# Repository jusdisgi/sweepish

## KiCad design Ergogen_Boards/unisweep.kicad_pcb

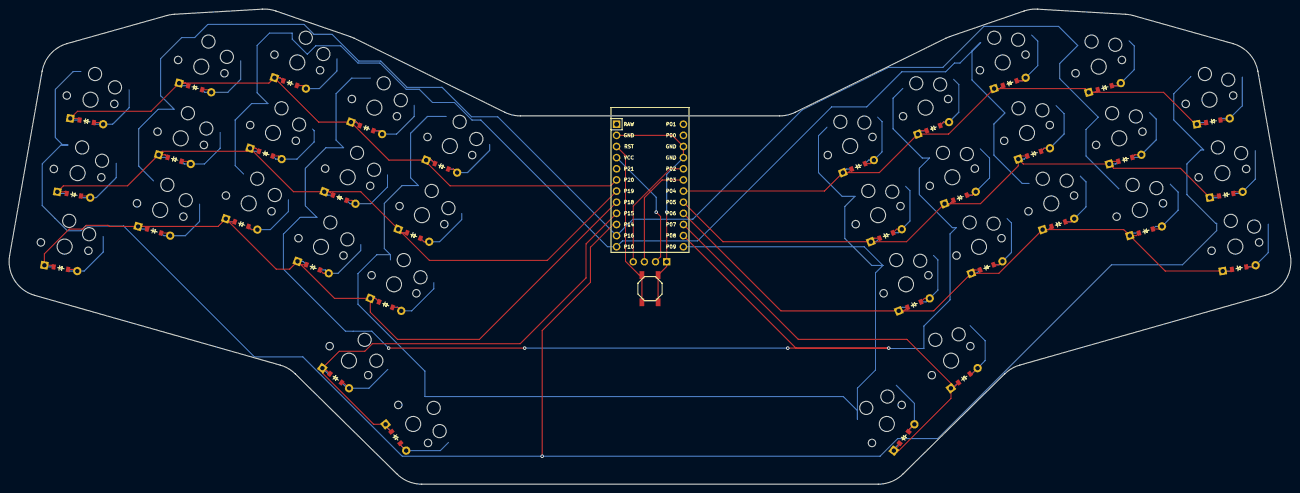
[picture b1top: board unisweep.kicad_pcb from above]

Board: 2 copper layers, 292.3 x 108.3 mm, 71 parts (0 on the bottom side), 52 nets.

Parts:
B1: SW_TACT_ALPS_SKQGABE010
D1, D2, D3, D4, D5, D6, D7, D8, D9, D10, D11, D12, D13, D14, D15, D16, D17, D18, D19, D20, D21, D22, D23, D24, D25, D26, D27, D28, D29, D30, D31, D32, D33, D34: ComboDiode
MCU1: ProMicro
OLED1: OLED; OLED_headers
S1, S2, S3, S4, S5, S6, S7, S8, S9, S10, S11, S12, S13, S14, S15, S16, S17, S18, S19, S20, S21, S22, S23, S24, S25, S26, S27, S28, S29, S30, S31, S32, S33, S34: PG1350

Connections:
GND: B1.1, MCU1.2, MCU1.15, MCU1.16, OLED1.1
P2: MCU1.17, OLED1.4
P3: MCU1.18, OLED1.3
P4: D20.1, D23.1, D26.1, D29.1, D32.1, MCU1.19
P5: D19.1, D22.1, D25.1, D28.1, D31.1, MCU1.20
P6: D18.1, D21.1, D24.1, D27.1, D30.1, MCU1.21
P7: D33.1, D34.1, MCU1.22
P8: MCU1.23, S10.1, S11.1, S12.1, S16.1, S27.1, S28.1, S29.1, S33.1
P9: MCU1.24, S13.1, S14.1, S15.1, S17.1, S30.1, S31.1, S32.1, S34.1
P10: MCU1.12, S7.1, S8.1, S9.1, S24.1, S25.1, S26.1
P14: MCU1.10, S1.1, S2.1, S3.1, S18.1, S19.1, S20.1
P15: D16.1, D17.1, MCU1.9
P16: MCU1.11, S4.1, S5.1, S6.1, S21.1, S22.1, S23.1
P18: D1.1, D4.1, D7.1, D10.1, D13.1, MCU1.8
P19: D2.1, D5.1, D8.1, D11.1, D14.1, MCU1.7
P20: D3.1, D6.1, D9.1, D12.1, D15.1, MCU1.6
RST: B1.2, MCU1.3
VCC: MCU1.4, OLED1.2
index_bottom: D10.2, S10.2
index_home: D11.2, S11.2
index_top: D12.2, S12.2
inner_bottom: D13.2, S13.2
inner_home: D14.2, S14.2
inner_top: D15.2, S15.2
left_onerow: D16.2, S16.2
middle_bottom: D7.2, S7.2
middle_home: D8.2, S8.2
middle_top: D9.2, S9.2
mirror_index_bottom: D27.2, S27.2
mirror_index_home: D28.2, S28.2
mirror_index_top: D29.2, S29.2
mirror_inner_bottom: D30.2, S30.2
mirror_inner_home: D31.2, S31.2
mirror_inner_top: D32.2, S32.2
mirror_left_onerow: D33.2, S33.2
mirror_middle_bottom: D24.2, S24.2
mirror_middle_home: D25.2, S25.2
mirror_middle_top: D26.2, S26.2
mirror_pinky_bottom: D18.2, S18.2
mirror_pinky_home: D19.2, S19.2
mirror_pinky_top: D20.2, S20.2
mirror_right_onerow: D34.2, S34.2
mirror_ring_bottom: D21.2, S21.2
mirror_ring_home: D22.2, S22.2
mirror_ring_top: D23.2, S23.2
pinky_bottom: D1.2, S1.2
pinky_home: D2.2, S2.2
pinky_top: D3.2, S3.2
right_onerow: D17.2, S17.2
ring_bottom: D4.2, S4.2
ring_home: D5.2, S5.2
ring_top: D6.2, S6.2
